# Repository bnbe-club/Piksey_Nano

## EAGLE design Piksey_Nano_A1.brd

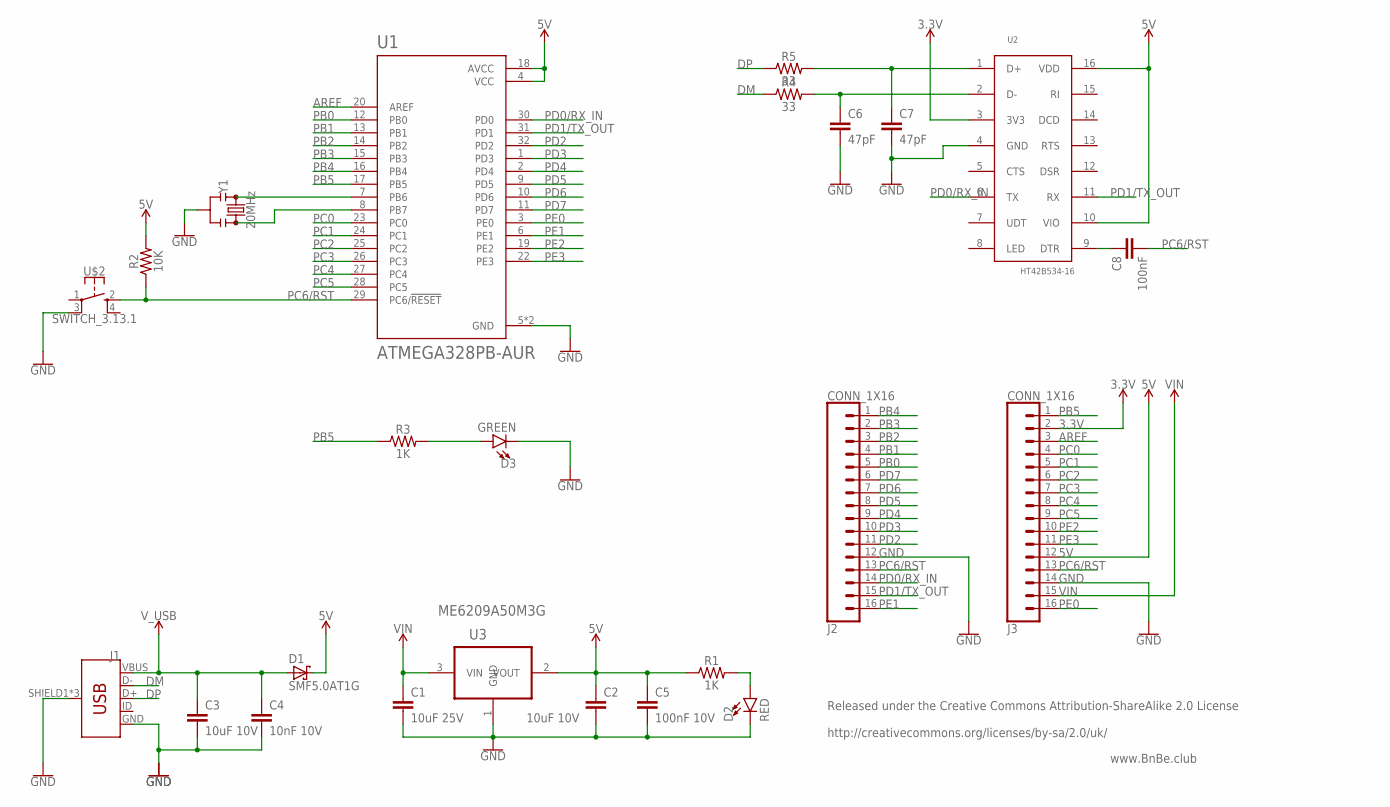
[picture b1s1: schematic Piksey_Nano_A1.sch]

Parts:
C1: 10uF 25V; 0603
C2, C3: 10uF 10V; 0402
C4: 10nF 10V; 0402
C5: 100nF 10V; 0402
C6, C7: 47pF; 0402
C8: 100nF; 0402
D1: SMF5.0AT1G; SOD123FL
D2: RED; LED-0603
D3: GREEN; LED-0603
J1: USB_MICRO-B_FEMALE-SMT; USB-B-MICRO-SMD
J2, J3: CONN_1X16; 1X16
R1, R3: 1K; 0402
R2: 10K; 0402
R4, R5: 33; 0402
U1: ATMEGA328PB-AUR; QFP80P900X900X120-32N
U2: HT42B534-16; NSOP-16
U3: ME6209A50M3G; SOT95P237X112-3N
U$2: SWITCH_3.13.1; SWITCH_3.1X3.1
Y1: 20MHz; RESONATOR-SMD-3.2X1.3

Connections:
3.3V: J3.2, U2.3 (3V3)
5V: C2.1, C5.1, D1.C, J3.12, R1.1, R2.2, U1.4 (VCC), U1.18 (AVCC), U2.10 (VIO), U2.16 (VDD), U3.2 (VOUT)
AREF: J3.3, U1.20 (AREF)
DM: J1.D-, R4.1
DP: J1.D+, R5.1
GND: C1.2, C2.2, C3.2, C4.2, C5.2, C6.2, C7.2, D2.C, D3.C, J1.GND, J1.SHIELD1 (SHIELD), J1.SHIELD2 (SHIELD), J1.SHIELD3 (SHIELD), J2.12, J3.14, U1.5 (GND), U1.21 (GND), U2.4 (GND), U3.1 (GND), U$2.3 (2), Y1.2
unnamed: C7.1, R5.2, U2.1 (D+)
unnamed: U1.7 (PB6), Y1.1
unnamed: C8.1, U2.9 (DTR)
unnamed: U1.8 (PB7), Y1.3
unnamed: D2.A, R1.2
unnamed: C6.1, R4.2, U2.2 (D-)
unnamed: D3.A, R3.2
PB0: J2.5, U1.12 (PB0)
PB1: J2.4, U1.13 (PB1)
PB2: J2.3, U1.14 (PB2)
PB3: J2.2, U1.15 (PB3)
PB4: J2.1, U1.16 (PB4)
PB5: J3.1, R3.1, U1.17 (PB5)
PC0: J3.4, U1.23 (PC0)
PC1: J3.5, U1.24 (PC1)
PC2: J3.6, U1.25 (PC2)
PC3: J3.7, U1.26 (PC3)
PC4: J3.8, U1.27 (PC4)
PC5: J3.9, U1.28 (PC5)
PC6/RST: C8.2, J2.13, J3.13, R2.1, U1.29 (PC6/!RESET), U$2.2 (3)
PD0/RX_IN: J2.14, U1.30 (PD0), U2.6 (TX)
PD1/TX_OUT: J2.15, U1.31 (PD1), U2.11 (RX)
PD2: J2.11, U1.32 (PD2)
PD3: J2.10, U1.1 (PD3)
PD4: J2.9, U1.2 (PD4)
PD5: J2.8, U1.9 (PD5)
PD6: J2.7, U1.10 (PD6)
PD7: J2.6, U1.11 (PD7)
PE0: J3.16, U1.3 (PE0)
PE1: J2.16, U1.6 (PE1)
PE2: J3.10, U1.19 (PE2)
PE3: J3.11, U1.22 (PE3)
VIN: C1.1, J3.15, U3.3 (VIN)
V_USB: C3.1, C4.1, D1.A, J1.VBUS

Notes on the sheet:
www.BnBe.club
Released under the Creative Commons Attribution-ShareAlike 2.0 License http://creativecommons.org/licenses/by-sa/2.0/uk/

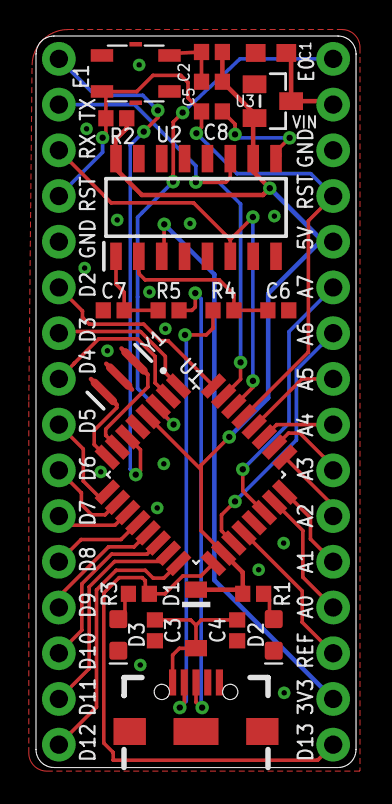
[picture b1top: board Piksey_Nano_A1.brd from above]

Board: 2 copper layers, 17.8 x 40.6 mm, 24 parts (0 on the bottom side), 40 nets.

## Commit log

2018-12-20 Initial commit.

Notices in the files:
parts and their libraries:
SparkFun-Capacitors: Licensing: Creative Commons ShareAlike 4.0 International - https://creativecommons.org/licenses/by-sa/4.0
